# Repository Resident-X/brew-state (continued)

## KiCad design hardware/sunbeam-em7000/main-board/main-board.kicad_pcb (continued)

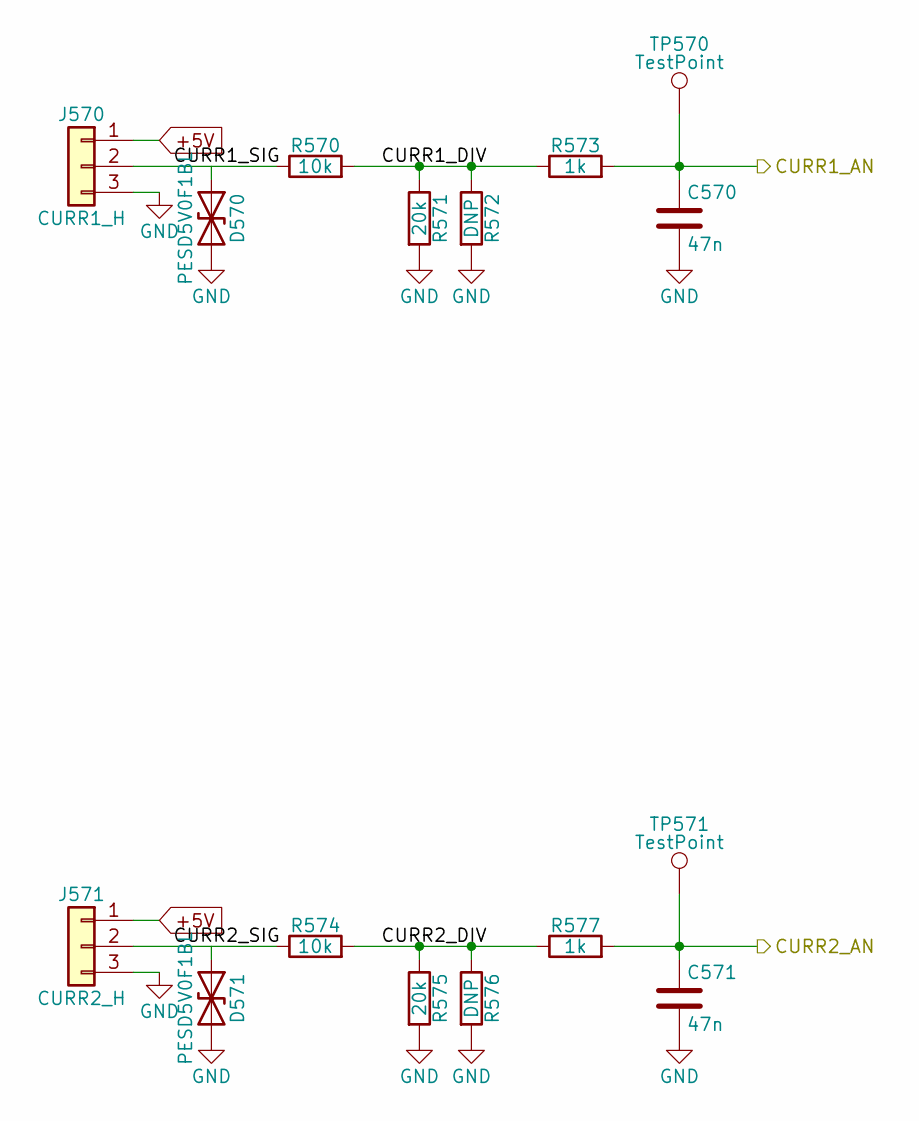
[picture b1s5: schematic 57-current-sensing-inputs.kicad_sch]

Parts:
C570, C571: 47n; C_0603_1608Metric; Rating 10% X7R 50V 0603; MPN CL10B473KB8NNNC; LCSC C1622
D570, D571: PESD5V0F1BL; D_SOD-882; Rating bidirectional 5.5V standoff, 0.55pF max; MPN PESD5V0F1BL,315; LCSC C45961
J570: CURR1_H; PinHeader_1x03_P2.54mm_Vertical; Rating 2.54mm 0.63mm pins; MPN 2.54mm 1x3 header; LCSC C49257
J571: CURR2_H; PinHeader_1x03_P2.54mm_Vertical; Rating 2.54mm 0.63mm pins; MPN 2.54mm 1x3 header; LCSC C49257
R570, R574: 10k; R_0603_1608Metric; Rating 1% 100ppm/K 0603 100mW; MPN 0603WAF1002T5E; LCSC C25804
R571, R575: 20k; R_0603_1608Metric; Rating 1% 100ppm/K 0603 100mW; MPN 0603WAF2002T5E; LCSC C4184
R572, R576: DNP; R_0603_1608Metric; Rating 1% 100ppm/K 0603 100mW; MPN 0603WAF1002T5E; LCSC C25804
R573, R577: 1k; R_0603_1608Metric; Rating 1% 100ppm/K 0603 100mW; MPN 0603WAF1001T5E; LCSC C21190
TP570, TP571: TestPoint; TestPoint_Pad_D1.5mm; Rating pad 1.5mm; LCSC none

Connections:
/CURR1_AN: C570.1, R573.2, TP570.1 (1_1); also elsewhere on the board
/CURR2_AN: C571.1, R577.2, TP571.1 (1_1); also elsewhere on the board
/Current sensing inputs/CURR1_DIV: R570.2, R571.1, R572.1, R573.1
/Current sensing inputs/CURR1_SIG: D570.1 (A1), J570.2, R570.1
/Current sensing inputs/CURR2_DIV: R574.2, R575.1, R576.1, R577.1
/Current sensing inputs/CURR2_SIG: D571.1 (A1), J571.2, R574.1
GND: C570.2, C571.2, D570.2 (A2), D571.2 (A2), J570.3, J571.3, R571.2, R572.2, R575.2, R576.2; also elsewhere on the board

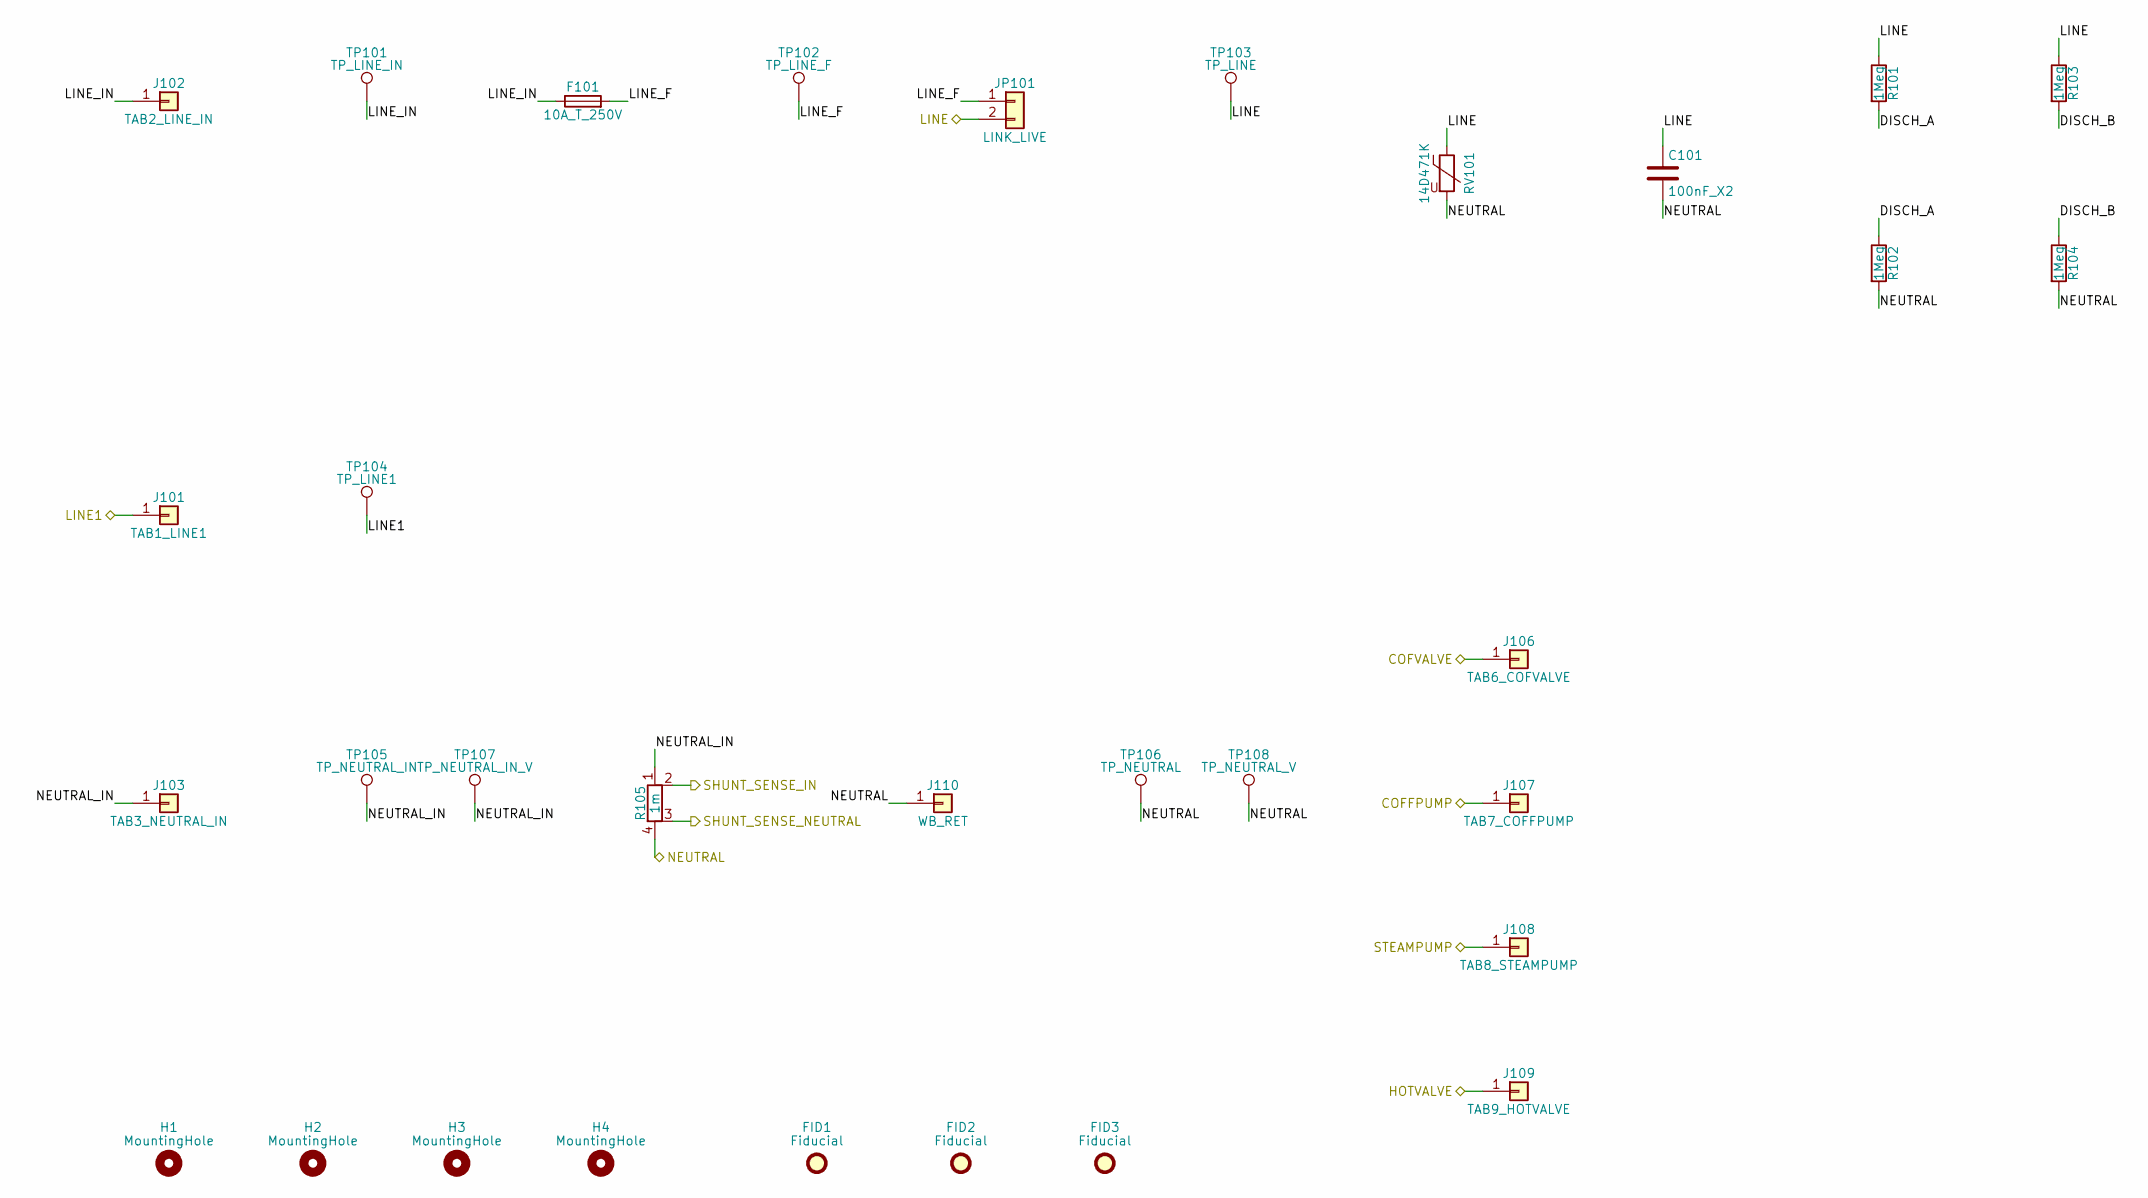
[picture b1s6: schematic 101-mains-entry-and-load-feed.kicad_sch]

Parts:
C101: 100nF_X2; C_Rect_L13.0mm_W6.0mm_P10.00mm_FKS3_FKP3_MKS4; Rating X2, 0.1 uF +-10 %, 310 VAC, -40..110 C,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; MPN MPX104K31C3KN15600; LCSC C489079
F101: 10A_T_250V; Fuseholder_Clip-5x20mm_Bel_FC-203-22_Lateral_P17.80x5.00mm_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; Rating SETfuse SCT520 plain 10 A 250 VAC (brea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; MPN SCT520T10A250V; LCSC C22447847
FID1, FID2, FID3: Fiducial; Fiducial_1mm_Mask2mm; Rating global fiducial, 1 mm copper, 2 mm mask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; LCSC none
H1, H2, H3, H4: MountingHole; MountingHole_3.1mm_Lid; Rating M3 lid screw, 3.1 mm non-plated hole; LCSC none
J101: TAB1_LINE1; Tab_BZXC_BTC-3-PCB634908T; Rating 6.3 x 0.8 mm blade, retained red lead (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; MPN BTC-3-PCB634908T; LCSC C20626104
J102: TAB2_LINE_IN; Tab_BZXC_BTC-3-PCB634908T; Rating 6.3 x 0.8 mm blade, retained brown lead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; MPN BTC-3-PCB634908T; LCSC C20626104
J103: TAB3_NEUTRAL_IN; Tab_BZXC_BTC-3-PCB634908T; Rating 6.3 x 0.8 mm blade, retained blue lead 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; MPN BTC-3-PCB634908T; LCSC C20626104
J106: TAB6_COFVALVE; Tab_BZXC_BTC-3-PCB634908T; Rating 6.3 x 0.8 mm blade, retained brown lead; MPN BTC-3-PCB634908T; LCSC C20626104
J107: TAB7_COFFPUMP; Tab_BZXC_BTC-3-PCB634908T; Rating 6.3 x 0.8 mm blade, retained white lead; MPN BTC-3-PCB634908T; LCSC C20626104
J108: TAB8_STEAMPUMP; Tab_BZXC_BTC-3-PCB634908T; Rating 6.3 x 0.8 mm blade, retained black lead; MPN BTC-3-PCB634908T; LCSC C20626104
J109: TAB9_HOTVALVE; Tab_BZXC_BTC-3-PCB634908T; Rating 6.3 x 0.8 mm blade, retained blue lead; MPN BTC-3-PCB634908T; LCSC C20626104
J110: WB_RET; Tab_BZXC_BTC-3-PCB634908T; Rating 6.3 x 0.8 mm blade, same part as the ta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; MPN BTC-3-PCB634908T; LCSC C20626104
JP101: LINK_LIVE; JP101_WireLink_P10mm; Rating first-power link position: two plated h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; MPN none (owner-fitted 1.5 mm2 wire); LCSC none
R101, R102, R103, R104: 1Meg; R_1206_3216Metric; Rating 1 % 1206 250 mW, 200 V max working; MPN 1206W4F1004T5E; LCSC C17927
R105: 1m; R_WSK2512_4T; Rating 1 mohm +-1 %, 2512 4-terminal, P70 1.0 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; MPN WSK25121L000FEA; LCSC C4248455
RV101: 14D471K; RV_Disc_D15.5mm_W5mm_P7.5mm; Rating 300 VAC max, 470 V class 14 mm disc, 42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; MPN 14D471K; LCSC C8852
TP101: TP_LINE_IN; TestPoint_Pad_D1.0mm_Tight; Rating mains copper; LCSC none
TP102: TP_LINE_F; TestPoint_Pad_D1.0mm_Tight; Rating mains copper; LCSC none
TP103: TP_LINE; TestPoint_Pad_D1.0mm_Tight; Rating mains copper; LCSC none
TP104: TP_LINE1; TestPoint_Pad_D1.0mm_Tight; Rating mains copper; LCSC none
TP105: TP_NEUTRAL_IN; TestPoint_Pad_D1.0mm_Tight; Rating mains copper; LCSC none
TP106: TP_NEUTRAL; TestPoint_Pad_D1.0mm_Tight; Rating mains copper; LCSC none
TP107: TP_NEUTRAL_IN_V; TestPoint_Pad_D1.0mm_Tight; Rating mains copper; LCSC none
TP108: TP_NEUTRAL_V; TestPoint_Pad_D1.0mm_Tight; Rating mains copper; LCSC none

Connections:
/COFFPUMP: J107.1 (Pin_1_1); also elsewhere on the board
/COFVALVE: J106.1 (Pin_1_1); also elsewhere on the board
/HOTVALVE: J109.1 (Pin_1_1); also elsewhere on the board
/LINE: C101.1, JP101.2, R101.1, R103.1, RV101.1, TP103.1 (1_1); also elsewhere on the board
/LINE1: J101.1 (Pin_1_1), TP104.1 (1_1); also elsewhere on the board
/Mains entry and load feed/DISCH_A: R101.2, R102.1
/Mains entry and load feed/DISCH_B: R103.2, R104.1
/Mains entry and load feed/LINE_F: F101.2, JP101.1, TP102.1 (1_1)
/Mains entry and load feed/LINE_IN: F101.1, J102.1 (Pin_1_1), TP101.1 (1_1)
/Mains entry and load feed/NEUTRAL_IN: J103.1 (Pin_1_1), R105.1, TP105.1 (1_1), TP107.1 (1_1)
/SHUNT_SENSE_IN: R105.2; also elsewhere on the board
/SHUNT_SENSE_NEUTRAL: R105.3; also elsewhere on the board
/STEAMPUMP: J108.1 (Pin_1_1); also elsewhere on the board

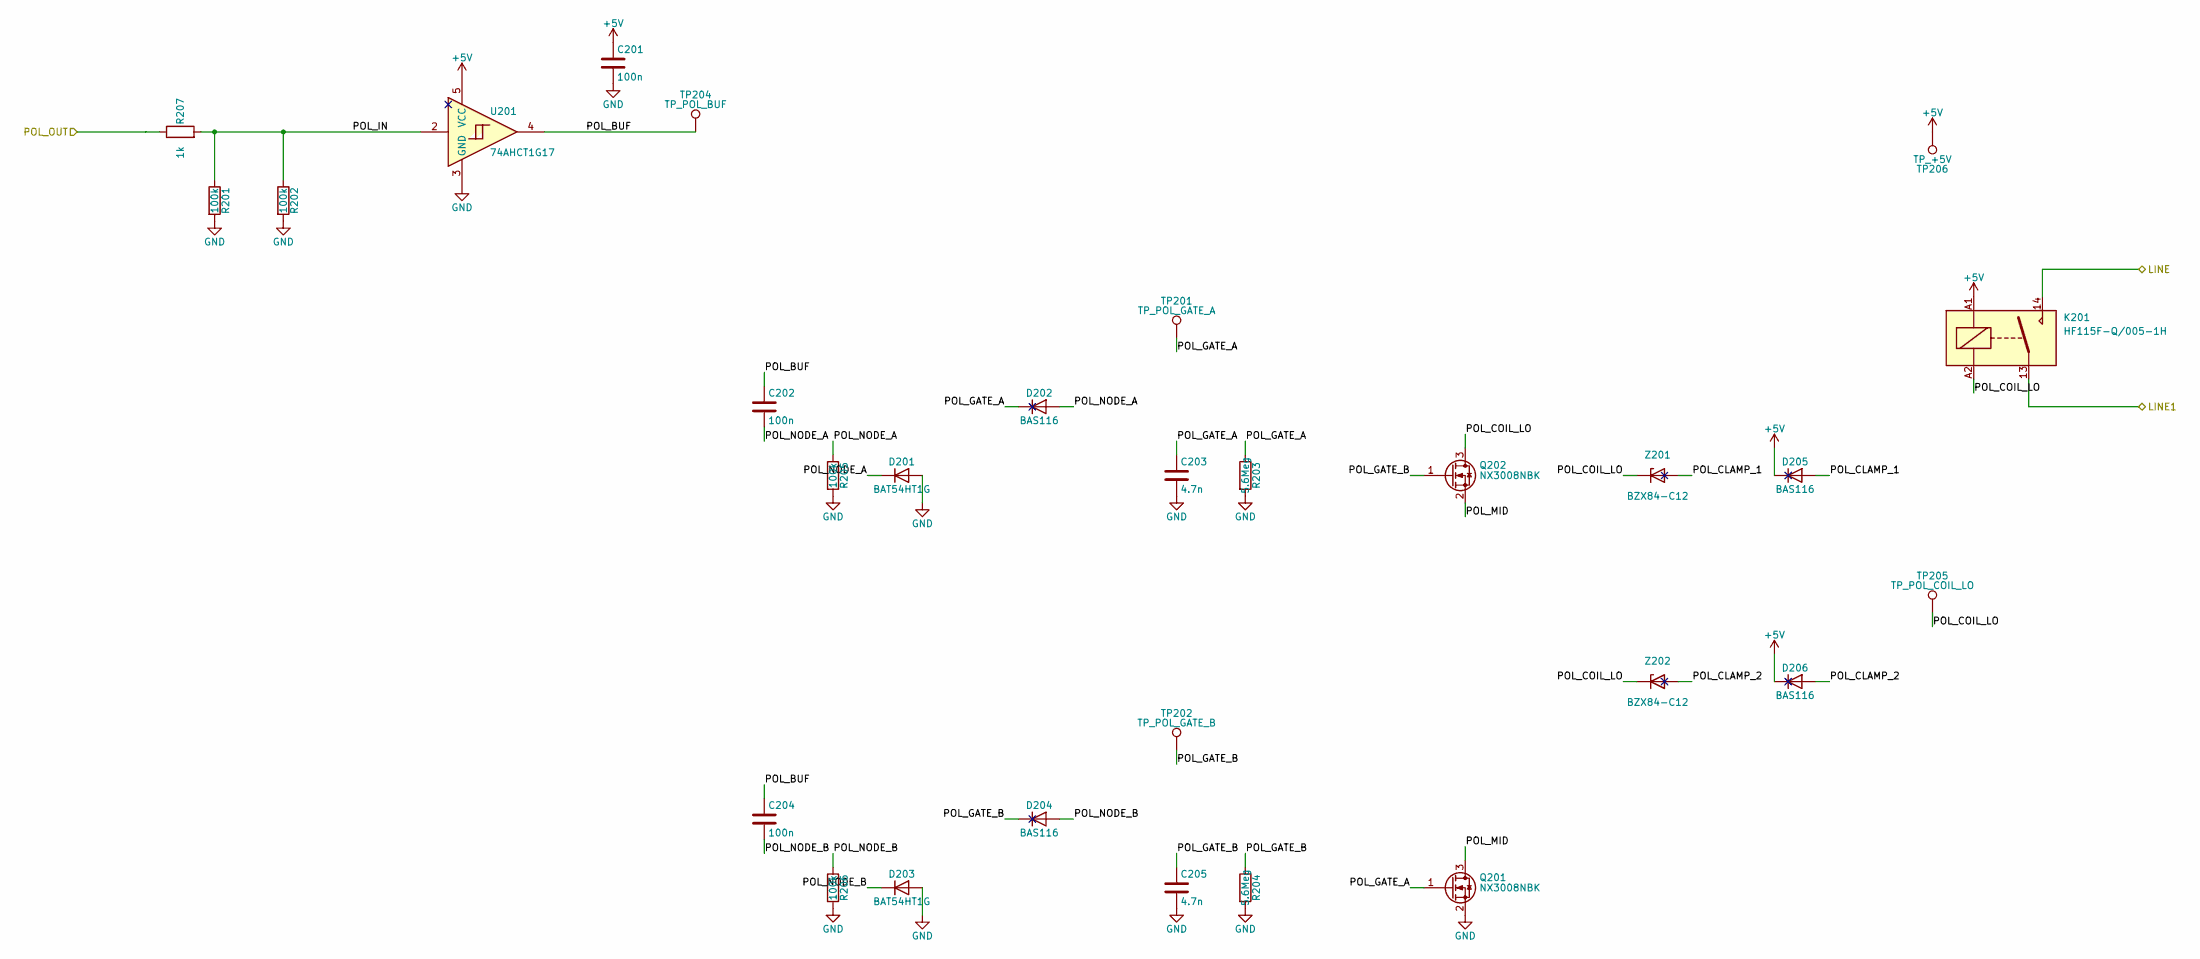
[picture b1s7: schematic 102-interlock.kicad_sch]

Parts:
C201: 100n; C_0603_1608Metric; Rating X7R 50 V 0603 10 %; MPN CC0603KRX7R9BB104; LCSC C14663
C202, C204: 100n; C_1206_3216Metric; Rating C0G 50 V +-5 % 1206; MPN GRM31C5C1H104JA01L; LCSC C97946
C203, C205: 4.7n; C_0603_1608Metric; Rating C0G 50 V +-5 % 0603; MPN GRM1885C1H472JA01D; LCSC C85980
D201, D203: BAT54HT1G; D_SOD-323; Rating Schottky 30 V, VF 0.32 V max at 1 mA; MPN BAT54HT1G; LCSC C21107
D202: BAS116; SOT-23; Rating low-leakage switching diode 85 V, VF 0.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; MPN BAS116,215; LCSC C48502
D204, D205: BAS116; SOT-23; Rating low-leakage switching diode, pin 1 anod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; MPN BAS116,215; LCSC C48502
D206: BAS116; SOT-23; Rating low-leakage switching diode; MPN BAS116,215; LCSC C48502
K201: HF115F-Q/005-1H; Relay_HF115F-Q_1H_Vertical; Rating 440 VAC max, 1 Form A AgNi, coil 5 V 62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; MPN HF115F-Q/005-1H; LCSC none
Q201: NX3008NBK; SOT-23; Rating N-FET 30 V, VGSth 0.6-1.1 V at 250 uA, 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; MPN NX3008NBK,215; LCSC C179399
Q202: NX3008NBK; SOT-23; Rating N-FET 30 V; MPN NX3008NBK,215; LCSC C179399
R201, R202, R205, R206: 100k; R_0603_1608Metric; Rating 1 % 0603 100 mW; MPN 0603WAF1003T5E; LCSC C25803
R203, R204: 5.6Meg; R_0603_1608Metric; Rating 1 % 0603 100 mW, 100 ppm/C; MPN 0603WAF5604T5E; LCSC C23190
R207: 1k; R_0603_1608Metric; Rating 1 % 0603 100 mW; MPN 0603WAF1001T5E; LCSC C21190
TP201: TP_POL_GATE_A; TestPoint_Pad_D1.0mm_Tight; LCSC none
TP202: TP_POL_GATE_B; TestPoint_Pad_D1.0mm_Tight; LCSC none
TP204: TP_POL_BUF; TestPoint_Pad_D1.0mm_Tight; LCSC none
TP205: TP_POL_COIL_LO; TestPoint_Pad_D1.0mm_Tight; LCSC none
TP206: TP_+5V; TestPoint_Pad_D1.0mm_Tight; LCSC none
U201: 74AHCT1G17; SOT-353_SC-70-5; Rating 7 V absolute maximum VCC, Schmitt non-i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; MPN 74AHCT1G17GW; LCSC C554579
Z201: BZX84-C12; SOT-23; Rating zener 12 V, 11.4-12.7 V at 5 mA, 250 mW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; MPN BZX84-C12,215; LCSC C108437
Z202: BZX84-C12; SOT-23; Rating zener 12 V; MPN BZX84-C12,215; LCSC C108437

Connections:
/Interlock/POL_BUF: C202.1, C204.1, TP204.1 (1_1), U201.4
/Interlock/POL_CLAMP_1: D205.1 (A), Z201.1 (A)
/Interlock/POL_CLAMP_2: D206.1 (A), Z202.1 (A)
/Interlock/POL_COIL_LO: K201.A2, Q202.3 (D), TP205.1 (1_1), Z201.3 (K), Z202.3 (K)
/Interlock/POL_GATE_A: C203.1, D202.3 (K), Q201.1 (G), R203.1, TP201.1 (1_1)
/Interlock/POL_GATE_B: C205.1, D204.3 (K), Q202.1 (G), R204.1, TP202.1 (1_1)
/Interlock/POL_IN: R201.1, R202.1, R207.2, U201.2
/Interlock/POL_MID: Q201.3 (D), Q202.2 (S)
/Interlock/POL_NODE_A: C202.2, D201.1 (K), D202.1 (A), R205.1
/Interlock/POL_NODE_B: C204.2, D203.1 (K), D204.1 (A), R206.1
/LINE: K201.14; also elsewhere on the board
/LINE1: K201.13; also elsewhere on the board
/POL_OUT: R207.1; also elsewhere on the board
GND: C201.2, C203.2, C205.2, D201.2 (A), D203.2 (A), Q201.2 (S), R201.2, R202.2, R203.2, R204.2, R205.2, R206.2, U201.3 (GND); also elsewhere on the board

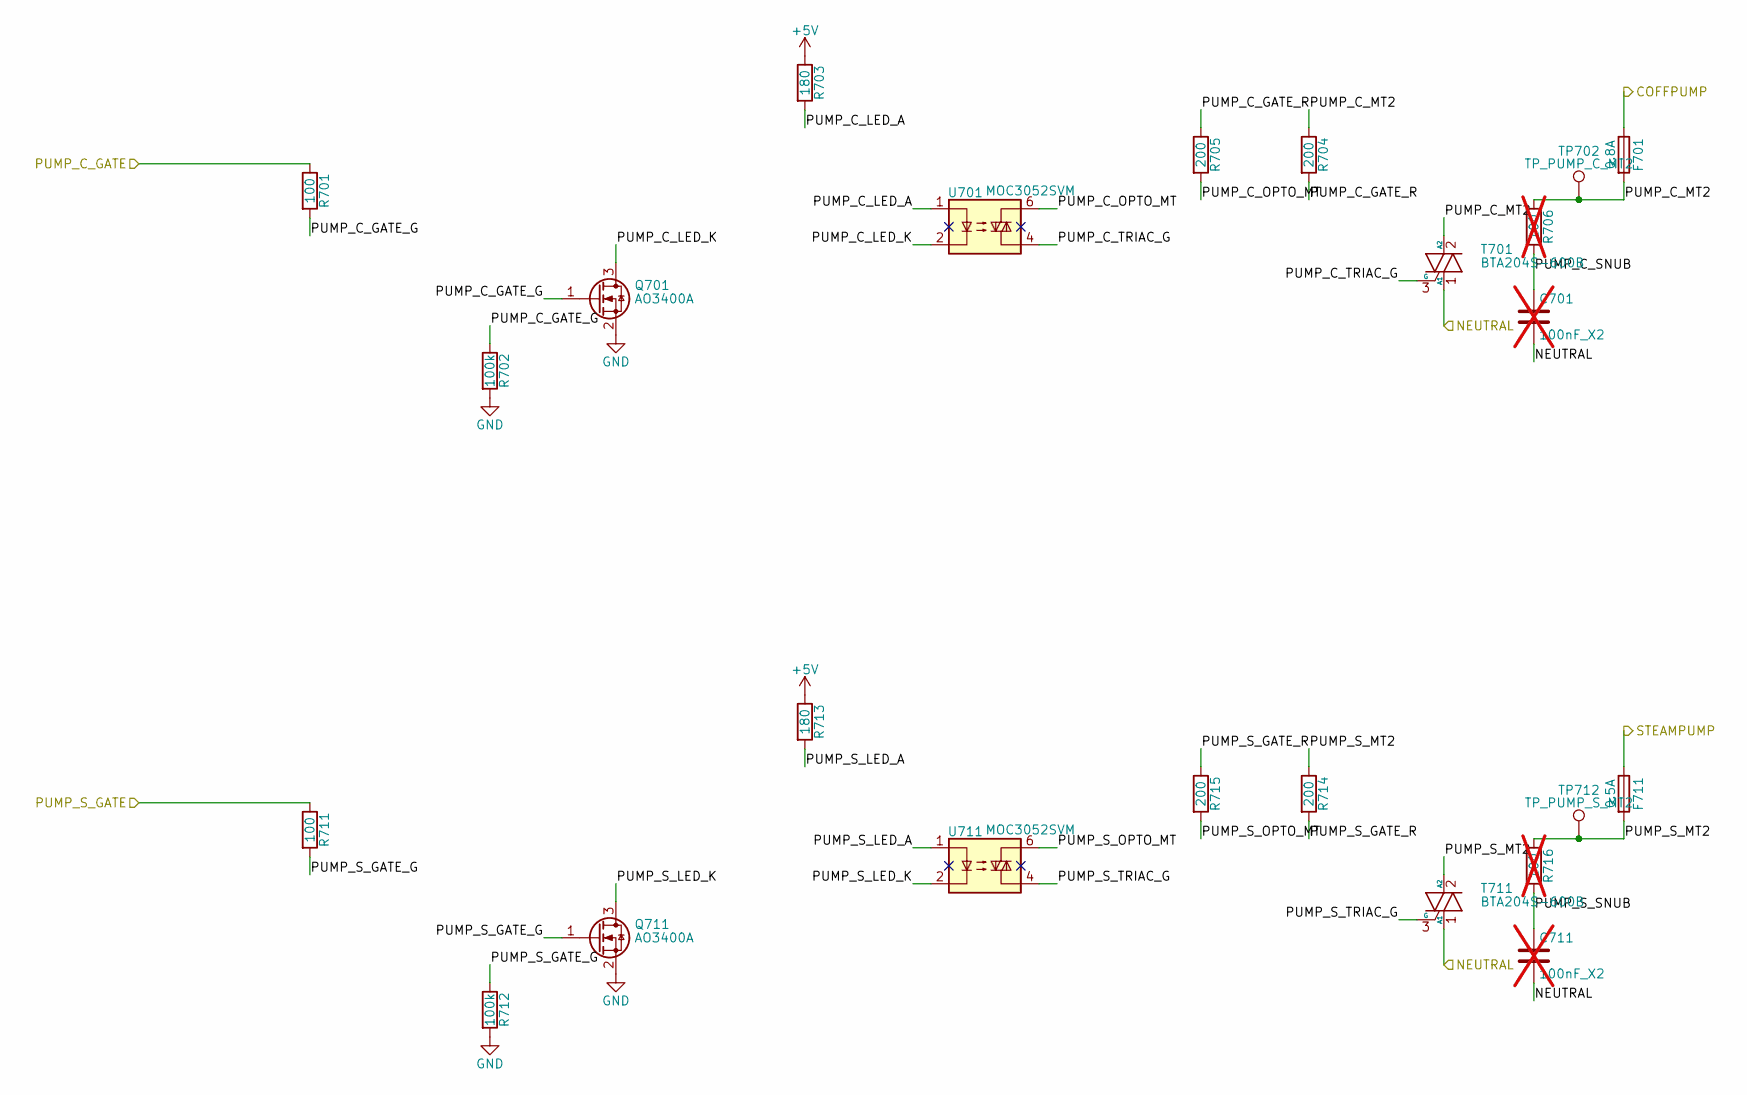
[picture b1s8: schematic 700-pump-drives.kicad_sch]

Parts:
C701, C711: 100nF_X2; C_Rect_L13.0mm_W6.0mm_P10.00mm_FKS3_FKP3_MKS4; Rating X2, 0.1 uF +-10 %, 310 VAC, -40..110 C,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; MPN MPX104K31C3KN15600; LCSC C489079; not fitted
F701: 0.8A; FUSEHOLDER_5x20_XC_BLX-A; Rating 5x20 mm (5.2 x 20) slow-blow 250 VAC ca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; MPN SCT520T0.8A250V; LCSC C3131
F711: 0.5A; FUSEHOLDER_5x20_XC_BLX-A; Rating 5x20 mm (5.2 x 20) slow-blow 250 VAC ca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; MPN SCT520T0.5A250V; LCSC C3131
Q701, Q711: AO3400A; SOT-23; Rating 30V 5.7A, RDS(on) <48 mohm at VGS 2.5 V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; MPN AO3400A; LCSC C20917
R701, R711: 100; R_0603_1608Metric; Rating 1% 100mW 75V 0603; MPN 0603WAF1000T5E; LCSC C22775
R702, R712: 100k; R_0603_1608Metric; Rating 1% 100mW 75V 0603; MPN 0603WAF1003T5E; LCSC C25803
R703, R713: 180; R_1206_3216Metric; Rating 1% 250mW 200V 1206; MPN 1206W4F1800T5E; LCSC C17924
R704, R705, R714, R715: 200; R_1206_3216Metric; Rating 1% 250mW 200V 1206; MPN 1206W4F2000T5E; LCSC C18002
R706, R716: 100; R_2512_6332Metric; Rating 1% 1W 200V 2512 thick film, 100 ohm; MPN 25121WF1000T4E; LCSC C35218; not fitted
T701, T711: BTA204S-600B; TO-252-2_TabPin2_Triac; Rating 600 V 4 A snubberless 3Q Hi-Com triac, 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; MPN BTA204S-600B,118; LCSC C256462
TP702: TP_PUMP_C_MT2; TestPoint_Pad_D1.0mm_Tight; Rating mains copper; LCSC none
TP712: TP_PUMP_S_MT2; TestPoint_Pad_D1.0mm_Tight; Rating mains copper; LCSC none
U701, U711: MOC3052SVM; MOC3052SVM_SMD-6; Rating 600 V random-phase triac driver, IFT ma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; MPN MOC3052SVM; LCSC C899826

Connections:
/COFFPUMP: F701.1; also elsewhere on the board
/PUMP_C_GATE: R701.1; also elsewhere on the board
/PUMP_S_GATE: R711.1; also elsewhere on the board
/Pump drives/PUMP_C_GATE_G: Q701.1 (G), R701.2, R702.1
/Pump drives/PUMP_C_GATE_R: R704.2, R705.1
/Pump drives/PUMP_C_LED_A: R703.2, U701.1
/Pump drives/PUMP_C_LED_K: Q701.3 (D), U701.2
/Pump drives/PUMP_C_MT2: F701.2, R704.1, R706.1, T701.2 (A2), TP702.1 (1_1)
/Pump drives/PUMP_C_OPTO_MT: R705.2, U701.6
/Pump drives/PUMP_C_SNUB: C701.1, R706.2
/Pump drives/PUMP_C_TRIAC_G: T701.3 (G), U701.4
/Pump drives/PUMP_S_GATE_G: Q711.1 (G), R711.2, R712.1
/Pump drives/PUMP_S_GATE_R: R714.2, R715.1
/Pump drives/PUMP_S_LED_A: R713.2, U711.1
/Pump drives/PUMP_S_LED_K: Q711.3 (D), U711.2
/Pump drives/PUMP_S_MT2: F711.2, R714.1, R716.1, T711.2 (A2), TP712.1 (1_1)
/Pump drives/PUMP_S_OPTO_MT: R715.2, U711.6
/Pump drives/PUMP_S_SNUB: C711.1, R716.2
/Pump drives/PUMP_S_TRIAC_G: T711.3 (G), U711.4
/STEAMPUMP: F711.1; also elsewhere on the board
GND: Q701.2 (S), Q711.2 (S), R702.2, R712.2; also elsewhere on the board

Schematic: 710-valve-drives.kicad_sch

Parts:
D731, D741: 1N4148WS; D_SOD-323; Rating 100 V 300 mA, SOD-323; MPN 1N4148WS; LCSC C2128
F731: 0.4A; FUSEHOLDER_5x20_XC_BLX-A; Rating 5x20 mm (5.2 x 20) slow-blow 250 VAC ca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; MPN SCT520T0.4A250V; LCSC C3131
K731, K741: HF32FA-G/005-HSL1; RELAY_HF32FA-G_1H_TYPE1_THT; Rating 10 A 250 VAC AgSnO2 contacts, 5 V sensi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; MPN HF32FA-G/005-HSL1; LCSC C91370
Q731, Q741: AO3400A; SOT-23; Rating 30V 5.7A, RDS(on) <48 mohm at VGS 2.5 V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; MPN AO3400A; LCSC C20917
R731, R741: 100; R_0603_1608Metric; Rating 1% 100mW 75V 0603; MPN 0603WAF1000T5E; LCSC C22775
R732, R742: 100k; R_0603_1608Metric; Rating 1% 100mW 75V 0603; MPN 0603WAF1003T5E; LCSC C25803
TP731, TP741: TP; TestPoint_Pad_D1.0mm_Tight; Rating test point; LCSC none

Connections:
/COFVALVE: K731.13; also elsewhere on the board
/HOTVALVE: K741.13; also elsewhere on the board
/VALVE_2W_DRV: R731.1, TP731.1 (1_1); also elsewhere on the board
/VALVE_3W_DRV: R741.1, TP741.1 (1_1); also elsewhere on the board
/Valve drives/VALVE_2W_COIL_K: D731.2 (A), K731.A2, Q731.3 (D)
/Valve drives/VALVE_2W_G: Q731.1 (G), R731.2, R732.1
/Valve drives/VALVE_3W_COIL_K: D741.2 (A), K741.A2, Q741.3 (D)
/Valve drives/VALVE_3W_G: Q741.1 (G), R741.2, R742.1
/Valve drives/VALVE_COM: F731.1, K731.14, K741.14
GND: Q731.2 (S), Q741.2 (S), R732.2, R742.2; also elsewhere on the board

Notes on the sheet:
Valve drives: two 5 V relays switch the valve coils' neutral-side leads (K731 above K741), low-side coil drivers, shared valve fuse F731.
MAINS: relay contacts 13-14, VALVE_COM, F731, NEUTRAL (left of the relays)
LOW VOLTAGE: +5V coil, AO3400A driver, 1N4148WS flyback (cathode on +5V), 100 R gate series, 100 k pull-down

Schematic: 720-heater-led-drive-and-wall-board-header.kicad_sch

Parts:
J761: WB_LV10; PinHeader_1x10_P2.54mm_Vertical; Rating 1x10 2.54 mm pin header, 3 A, vertical; MPN 2.54-1*10PPin; LCSC C57369
JP761: LINK; PinHeader_1x02_P2.54mm_Vertical; Rating 1x2 2.54 mm header + shunt jumper, 3 A,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; MPN PH2.54-1X2P-H25 + 2.54 Short Circuit Ca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; LCSC C42431798
Q761, Q771: AO3400A; SOT-23; Rating 30V 5.7A, RDS(on) <48 mohm at VGS 2.5 V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; MPN AO3400A; LCSC C20917
R761, R771: 100; R_0603_1608Metric; Rating 1% 100mW 75V 0603; MPN 0603WAF1000T5E; LCSC C22775
R762, R772: 100k; R_0603_1608Metric; Rating 1% 100mW 75V 0603; MPN 0603WAF1003T5E; LCSC C25803
R763, R773: 180; R_1206_3216Metric; Rating 1% 250mW 200V 1206; MPN 1206W4F1800T5E; LCSC C17924
R764, R774: 27k; R_0603_1608Metric; Rating 1% 100mW 75V 0603; MPN 0603WAF2702T5E; LCSC C22967
R765, R775: 82k; R_0603_1608Metric; Rating 1% 100mW 75V 0603; MPN 0603WAF8202T5E; LCSC C23254
TP761, TP762, TP772: TP; TestPoint_Pad_D1.5mm; Rating test point; LCSC none

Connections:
+5V_WB: J761.1, JP761.2, TP761.1 (1_1)
/HEAT_C_DRV: R761.1, TP762.1 (1_1); also elsewhere on the board
/HEAT_S_DRV: R771.1, TP772.1 (1_1); also elsewhere on the board
/Heater LED drive and wall board header/HEAT_C_G: Q761.1 (G), R761.2, R762.1
/Heater LED drive and wall board header/HEAT_C_SINK: Q761.3 (D), R763.2
/Heater LED drive and wall board header/HEAT_S_G: Q771.1 (G), R771.2, R772.1
/Heater LED drive and wall board header/HEAT_S_SINK: Q771.3 (D), R773.2
/Heater LED drive and wall board header/MAINS_PRES_C_J: J761.5, R764.1
/Heater LED drive and wall board header/MAINS_PRES_S_J: J761.6, R774.1
/MAINS_PRES_C: R764.2, R765.1; also elsewhere on the board
/MAINS_PRES_S: R774.2, R775.1; also elsewhere on the board
GND: J761.4, Q761.2 (S), Q771.2 (S), R762.2, R765.2, R772.2, R775.2; also elsewhere on the board
HEAT_C_LED_K: J761.2, R763.1
HEAT_S_LED_K: J761.3, R773.1

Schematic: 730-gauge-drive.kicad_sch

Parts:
C791: 100n; C_0603_1608Metric; Rating 10% X7R 50V 0603; MPN CC0603KRX7R9BB104; LCSC C14663
C792: 47u; CP_Elec_5x5.4; Rating aluminium electrolytic 16 V +/-20 % 105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; MPN RST47UF16V034; LCSC C4747957
J791: SP2; JST_PH_B9B-PH-K_1x09_P2.00mm_Vertical; Rating 9-way 2.0 mm header JST B9B-PH-K-S, 2 A; MPN B9B-PH-K-S(LF)(SN); LCSC C157968
JP791: LINK; PinHeader_1x02_P2.54mm_Vertical; Rating 1x2 2.54 mm header + shunt jumper, 3 A,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; MPN PH2.54-1X2P-H25 + 2.54 Short Circuit Ca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; LCSC C42431798
R791, R792, R793, R794, R795: 470; R_0603_1608Metric; Rating 1% 100mW 75V 0603; MPN 0603WAF4700T5E; LCSC C23179
R796, R797, R798, R799, R800: 1k; R_0603_1608Metric; Rating 1% 100mW 75V 0603; MPN 0603WAF1001T5E; LCSC C21190
R801, R802, R803, R804, R805, R806: 10k; R_0603_1608Metric; Rating 1% 100mW 75V 0603; MPN 0603WAF1002T5E; LCSC C25804
TP791, TP792, TP793, TP794, TP795, TP796: TP; TestPoint_Pad_D1.0mm_Tight; Rating test point; LCSC none
U791: SN74HCT541PWR; TSSOP-20_4.4x6.5mm_P0.65mm; Rating 7 V absolute maximum VCC, octal buffer,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; MPN SN74HCT541PWR; LCSC C436096

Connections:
+5V_GAUGE: C792.1, J791.1, JP791.2, TP791.1 (1_1)
/ANODE_RAIL: J791.7; also elsewhere on the board
/GAUGE_DIR1: R798.1, TP794.1 (1_1); also elsewhere on the board
/GAUGE_DIR2: R800.1, TP796.1 (1_1); also elsewhere on the board
/GAUGE_RST: R796.1, TP792.1 (1_1); also elsewhere on the board
/GAUGE_STEP1: R797.1, TP793.1 (1_1); also elsewhere on the board
/GAUGE_STEP2: R799.1, TP795.1 (1_1); also elsewhere on the board
/Gauge drive/GAUGE_DIR1_B: J791.5, R793.2
/Gauge drive/GAUGE_DIR1_IN: R798.2, R803.1, U791.4 (A2)
/Gauge drive/GAUGE_DIR1_Y: R793.1, U791.16 (Y2)
/Gauge drive/GAUGE_DIR2_B: J791.8, R795.2
/Gauge drive/GAUGE_DIR2_IN: R800.2, R805.1, U791.6 (A4)
/Gauge drive/GAUGE_DIR2_Y: R795.1, U791.14 (Y4)
/Gauge drive/GAUGE_RST_B: J791.3, R791.2, R806.1
/Gauge drive/GAUGE_RST_IN: R796.2, R801.1, U791.2 (A0)
/Gauge drive/GAUGE_RST_Y: R791.1, U791.18 (Y0)
/Gauge drive/GAUGE_STEP1_B: J791.4, R792.2
/Gauge drive/GAUGE_STEP1_IN: R797.2, R802.1, U791.3 (A1)
/Gauge drive/GAUGE_STEP1_Y: R792.1, U791.17 (Y1)
/Gauge drive/GAUGE_STEP2_B: J791.9, R794.2
/Gauge drive/GAUGE_STEP2_IN: R799.2, R804.1, U791.5 (A3)
/Gauge drive/GAUGE_STEP2_Y: R794.1, U791.15 (Y3)
/LOWWATER_CATHODE: J791.6; also elsewhere on the board
GND: C791.2, C792.2, J791.2, R801.2, R802.2, R803.2, R804.2, R805.2, R806.2, U791.1 (G1), U791.7 (A5), U791.8 (A6), U791.9 (A7), U791.10 (GND), U791.19 (G2); also elsewhere on the board

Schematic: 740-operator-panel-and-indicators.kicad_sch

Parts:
D821: 1N4148WS; D_SOD-323; Rating 100 V 300 mA, SOD-323; MPN 1N4148WS; LCSC C2128
J821: CON2; JST_PH_B9B-PH-K_1x09_P2.00mm_Vertical; Rating 9-way 2.0 mm header JST B9B-PH-K-S, 2 A; MPN B9B-PH-K-S(LF)(SN); LCSC C157968
JP821: LINK; PinHeader_1x02_P2.54mm_Vertical; Rating 1x2 2.54 mm header + shunt jumper, 3 A,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; MPN PH2.54-1X2P-H25 + 2.54 Short Circuit Ca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; LCSC C42431798
Q821, Q823, Q824: AO3400A; SOT-23; Rating 30V 5.7A, RDS(on) <48 mohm at VGS 2.5 V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; MPN AO3400A; LCSC C20917
Q822: AO3401A; SOT-23; Rating -30 V -4 A P-channel, VGS(th) -0.5..-1.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; MPN AO3401A; LCSC C15127
R821, R826, R829: 100; R_0603_1608Metric; Rating 1% 100mW 75V 0603; MPN 0603WAF1000T5E; LCSC C22775
R822, R827, R830: 100k; R_0603_1608Metric; Rating 1% 100mW 75V 0603; MPN 0603WAF1003T5E; LCSC C25803
R823, R824, R825: 22k; R_0603_1608Metric; Rating 1% 100mW 75V 0603; MPN 0603WAF2202T5E; LCSC C31850
R828: 100; R_1206_3216Metric; Rating 1% 250mW 200V 1206; MPN 1206W4F1000T5E; LCSC C17901
R831, R832, R833, R834, R835: 10k; R_0603_1608Metric; Rating 1% 100mW 75V 0603; MPN 0603WAF1002T5E; LCSC C25804
TP821, TP824, TP831, TP832, TP833, TP834, TP835: TP; TestPoint_Pad_D1.0mm_Tight; Rating test point; LCSC none

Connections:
/ANODE_GATE: R821.1; also elsewhere on the board
/ANODE_RAIL: J821.7, JP821.2, R825.1; also elsewhere on the board
/BUZZER: R826.1; also elsewhere on the board
/KEY1: J821.3, R831.1, TP831.1 (1_1); also elsewhere on the board
/KEY2: J821.4, R832.1, TP832.1 (1_1); also elsewhere on the board
/KEY3: J821.5, R833.1, TP833.1 (1_1); also elsewhere on the board
/KEY4: J821.6, R834.1, TP834.1 (1_1); also elsewhere on the board
/KEY5: J821.8, R835.1, TP835.1 (1_1); also elsewhere on the board
/LOWWATER_CATHODE: Q824.3 (D); also elsewhere on the board
/LOWWATER_K: R829.1, TP824.1 (1_1); also elsewhere on the board
/Operator panel and indicators/ANODE_LS_G: Q821.1 (G), R821.2, R822.1
/Operator panel and indicators/ANODE_PG: Q821.3 (D), Q822.1 (G), R823.2, R824.2
/Operator panel and indicators/ANODE_SW: JP821.1, Q822.3 (D), TP821.1 (1_1)
/Operator panel and indicators/BUZZER_G: Q823.1 (G), R826.2, R827.1
/Operator panel and indicators/BUZZER_N: D821.2 (A), J821.2, Q823.3 (D)
/Operator panel and indicators/BUZZER_P: D821.1 (K), J821.1, R828.2
/Operator panel and indicators/LOWWATER_G: Q824.1 (G), R829.2, R830.1
GND: J821.9, Q821.2 (S), Q823.2 (S), Q824.2 (S), R822.2, R825.2, R827.2, R830.2; also elsewhere on the board

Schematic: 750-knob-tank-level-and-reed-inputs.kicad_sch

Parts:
C861, C862, C863: 100n; C_0603_1608Metric; Rating 10% X7R 50V 0603; MPN CC0603KRX7R9BB104; LCSC C14663
J861: KNOB; JST_PH_B4B-PH-K_1x04_P2.00mm_Vertical; Rating 4-way header, JST B4B-PH-K-S (2.00 mm; 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; MPN B4B-PH-K-S(LF)(SN); LCSC C131334
J862: REED; REED_PADS_P20.00mm; Rating two through-hole pads 20.0 mm apart for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; LCSC none
R861, R862, R863: 10k; R_0603_1608Metric; Rating 1% 100mW 75V 0603; MPN 0603WAF1002T5E; LCSC C25804
TP861: TP; TestPoint_Pad_D1.0mm_Tight; Rating test point; LCSC none

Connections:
/KNOB_HOT: C861.1, J861.1, R861.1, TP861.1 (1_1); also elsewhere on the board
/KNOB_STEAM: C862.1, J861.3, R862.1; also elsewhere on the board
/TANK_LEVEL: C863.1, J862.2, R863.1; also elsewhere on the board
GND: C861.2, C862.2, C863.2, J861.2, J861.4, J862.1; also elsewhere on the board

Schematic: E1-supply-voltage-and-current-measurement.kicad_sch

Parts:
C601, C602: 4.7n; C_0805_2012Metric; Rating C0G 50V 10% 0805; MPN C0805N472K050T; LCSC C105936
C603, C610: 1u; C_0603_1608Metric; Rating X7R 25V 10% 0603; MPN CC0603KRX7R8BB105; LCSC C106858
C604, C606, C608, C609: 1n; C_0603_1608Metric; Rating X7R 50V 10% 0603; MPN CL10B102KB8NNNC; LCSC C1588
C605, C611, C612: 100n; C_0603_1608Metric; Rating X7R 50V 10% 0603; MPN CL10B104KB8NNNC; LCSC C1591
C607: 100n; C_1206_3216Metric; Rating C0G 50V 5% 1206; MPN 1206N104J500CT; LCSC C170182
F601, F602: 600R@100MHz; L_0603_1608Metric; Rating 0603 350mA 0.5ohm; MPN FCM1608KF-601T03; LCSC C141723
NT601: NetTie_2; NetTie-2_SMD_Pad0.5mm; LCSC none
R601, R602, R603: 300k; R_2512_6332Metric; Rating 1% 100ppm 2512 1W 200V working, 400V ov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; MPN FRC2512F3003TS; LCSC C2960835
R604: 750; R_0603_1608Metric; Rating 1% 100ppm 0603 100mW; MPN 0603WAF7500T5E; LCSC C23241
R605, R606: 49.9; R_0603_1608Metric; Rating 1% 100ppm 0603 100mW; MPN 0603WAF499JT5E; LCSC C23185
R607, R608: 330; R_0603_1608Metric; Rating 1% 100ppm 0603 100mW; MPN 0603WAF3300T5E; LCSC C23138
R609, R610, R611, R612, R613: 33; R_0603_1608Metric; Rating 1% 100mW 75V 0603; MPN 0603WAF330JT5E; LCSC C23140
R614, R615: 100k; R_0603_1608Metric; Rating 1% 100mW 75V 0603; MPN 0603WAF1003T5E; LCSC C25803
TP602: TP_AMC_CLKIN; TestPoint_Pad_D1.0mm_Tight; LCSC none
TP603: TP_VMEAS_DIV; TestPoint_Pad_D1.0mm_Tight; LCSC none
TP604: TP_AMC_AIN1P; TestPoint_Pad_D1.0mm_Tight; LCSC none
TP605: TP_AMC_DCDC_OUT; TestPoint_Pad_D1.0mm_Tight; LCSC none
TP606: TP_AMC_DCDC_HGND; TestPoint_Pad_D1.0mm_Tight; LCSC none
TP607: TP_AMC_HLDO_IN; TestPoint_Pad_D1.0mm_Tight; LCSC none
TP608: TP_AMC_HLDO_OUT; TestPoint_Pad_D1.0mm_Tight; LCSC none
TP609: TP_AMC_DCDC_CAP; TestPoint_Pad_D1.0mm_Tight; LCSC none
TP610: TP_SPI2_MISO; TestPoint_Pad_D1.0mm_Tight; LCSC none
U601: AMC131M02; AMC131M02_SOIC-20W_DFM0020A; Rating reinforced isolation VIORM 1700 V pk, V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; MPN AMC131M02DFMR; LCSC C31423783
Y601: 8.000MHz; Oscillator_SMD_Abracon_ASE-4Pin_3.2x2.5mm_Pin1Mark; Rating 2.97-3.63 V supply range, 3.3 V LVCMOS,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; MPN SiT8008BI-22-33E-8.000000; LCSC C819601

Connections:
/AMC_CS: R612.1; also elsewhere on the board
/AMC_DRDY: U601.16 (~DRDY); also elsewhere on the board
/AMC_RESET: R615.2, U601.11 (~SYNC/~RESET); also elsewhere on the board
/LINE: R601.1; also elsewhere on the board
/SHUNT_SENSE_IN: R607.1; also elsewhere on the board
/SHUNT_SENSE_NEUTRAL: R608.1; also elsewhere on the board
/SPI2_MISO: R613.2, TP610.1 (1_1); also elsewhere on the board
/SPI2_MOSI: R611.1; also elsewhere on the board
/SPI2_SCK: R610.1; also elsewhere on the board
/Supply voltage and current measurement/AMC_AIN0N: C601.2, R606.1, U601.10 (AIN0N)
/Supply voltage and current measurement/AMC_AIN0P: C601.1, R605.2, U601.9 (AIN0P)
/Supply voltage and current measurement/AMC_AIN1N: C602.2, R608.2, U601.7 (AIN1N)
/Supply voltage and current measurement/AMC_AIN1P: C602.1, R607.2, TP604.1 (1_1), U601.8 (AIN1P)
/Supply voltage and current measurement/AMC_CLKIN: R609.2, TP602.1 (1_1), U601.17 (CLKIN)
/Supply voltage and current measurement/AMC_CLK_OUT: R609.1, Y601.3 (OUT)
/Supply voltage and current measurement/AMC_CS_PIN: R612.2, R614.2, U601.19 (~CS)
/Supply voltage and current measurement/AMC_DCDC_CAP: C612.1, TP609.1 (1_1), U601.14 (DCDC_CAP)
/Supply voltage and current measurement/AMC_DCDC_OUT: C603.1, C604.1, F601.1, TP605.1 (1_1), U601.1 (DCDC_OUT)
/Supply voltage and current measurement/AMC_DIN: R611.2, U601.20 (DIN)
/Supply voltage and current measurement/AMC_DOUT_PIN: R613.1, U601.12 (DOUT)
/Supply voltage and current measurement/AMC_HGND: C605.2, C606.2, C607.2, C608.2, F602.2, NT601.2, R604.2, R606.2, U601.5 (HGND)
/Supply voltage and current measurement/AMC_HLDO_OUT: C607.1, C608.1, TP608.1 (1_1), U601.4 (HLDO_OUT)
/Supply voltage and current measurement/AMC_SCLK: R610.2, U601.18 (SCLK)
/Supply voltage and current measurement/VMEAS_DIV: R603.2, R604.1, R605.1, TP603.1 (1_1)
/Supply voltage and current measurement/VMEAS_N1: R601.2, R602.1
/Supply voltage and current measurement/VMEAS_N2: R602.2, R603.1
GND: C609.2, C610.2, C611.2, C612.2, U601.15 (DGND), Y601.2 (GND); also elsewhere on the board

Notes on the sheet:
channel 0: supply voltage, gain 1
channel 1: supply current, gain 32

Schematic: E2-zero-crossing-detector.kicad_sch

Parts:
C630: 1n; C_0603_1608Metric; Rating X7R 50V 10% 0603; MPN CL10B102KB8NNNC; LCSC C1588
R630, R631: 60.4k; R_2512_6332Metric; Rating 1% 100ppm 2512 1W 200V working, 400V ov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; MPN FRC2512F6042TS; LCSC C5126066
R632: 22k; R_0603_1608Metric; Rating 1% 100mW 75V 0603; MPN 0603WAF2202T5E; LCSC C31850
TP630: TP_ZC_IN; TestPoint_Pad_D1.5mm; LCSC none
U602: LTV-814S-TA1-A; LTV-814S_SMD-4; Rating isolation 5000 VAC rms 1 min, AC input,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; MPN LTV-814S-TA1-A; LCSC C108051

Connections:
/LINE: R630.1; also elsewhere on the board
/ZC_IN: C630.1, R632.1, TP630.1 (1_1), U602.4 (C); also elsewhere on the board
/Zero-crossing detector/ZC_LED_A: R631.2, U602.1 (A/K)
/Zero-crossing detector/ZC_N1: R630.2, R631.1
GND: C630.2, U602.3 (E); also elsewhere on the board

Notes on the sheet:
The mains-presence inputs MAINS_PRES_C (PE15) and MAINS_PRES_S (PD7) are not drawn: no parts are placed for them. Their controller pins stay free and their header ways (WB_LV10 pins 5 and 6) are reserved by the wall-header sheet.
The LEDs are antiparallel, so the output falls once per half-cycle whatever the polarity; the supply's period is the time between like edges (capture on both edges).
mains | low voltage (optocoupler barrier)
